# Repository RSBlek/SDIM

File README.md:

# SDIM
Semi Dynamic Indicator Module

Eagle Files for VW Golf 7 Semi Dynamic Indicator Modules for led rear lights

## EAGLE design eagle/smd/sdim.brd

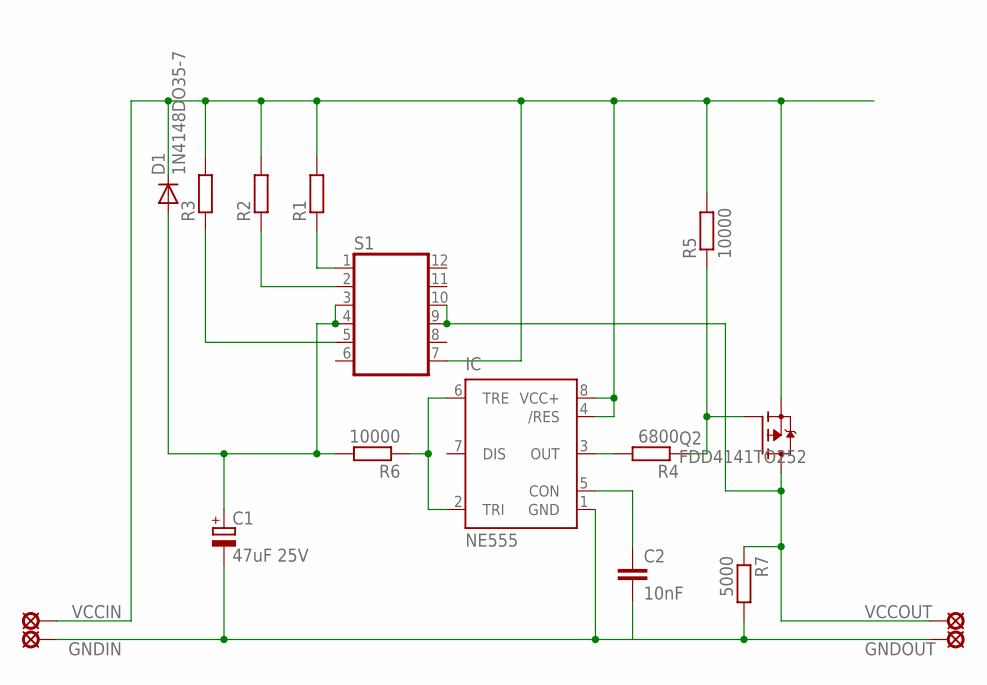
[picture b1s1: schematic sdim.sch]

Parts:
C1: 47uF 25V; E2,5-6
C2: 10nF; C1206
D1: 1N4148DO35-7; DO35-7
GNDIN: MCS10B
GNDOUT: MCS10B
IC: NE555; DIL-08
Q2: FDD4141TO252; TO252
R1, R2, R3: R-EU_R1206; R1206
R4: 6800; R1206
R5, R6: 10000; R1206
R7: 5000; R1206
S1: DA06; DA-06
VCCIN: MCS10B
VCCOUT: MCS10B

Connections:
unnamed: C1.-, C2.2, GNDIN.MP, GNDOUT.MP, IC.1 (GND), R7.2
unnamed: Q2.1 (G), R4.1, R5.1
unnamed: C2.1, IC.5 (CON)
unnamed: R1.1, S1.1
unnamed: R2.1, S1.2
unnamed: IC.3 (OUT), R4.2
unnamed: C1.+, D1.A, R6.2, S1.3, S1.4
unnamed: R3.1, S1.5
unnamed: Q2.3 (D), R7.1, S1.9, S1.10, VCCOUT.MP
unnamed: D1.C, IC.4 (/RES), IC.8 (VCC+), Q2.2 (S), R1.2, R2.2, R3.2, R5.2, S1.7, VCCIN.MP
unnamed: IC.2 (TRI), IC.6 (TRE), R6.1

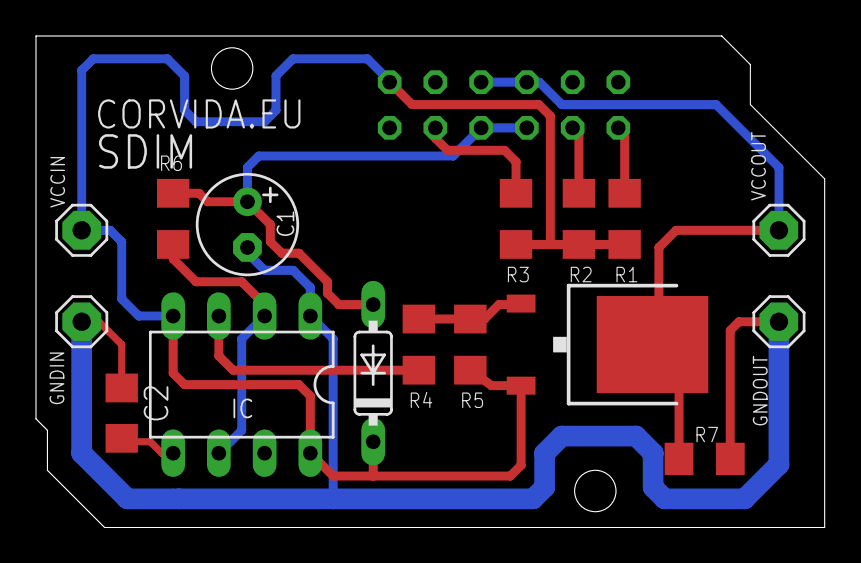
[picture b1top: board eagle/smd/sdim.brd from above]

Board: 2 copper layers, 43.8 x 27.3 mm, 17 parts (1 on the bottom side), 11 nets.

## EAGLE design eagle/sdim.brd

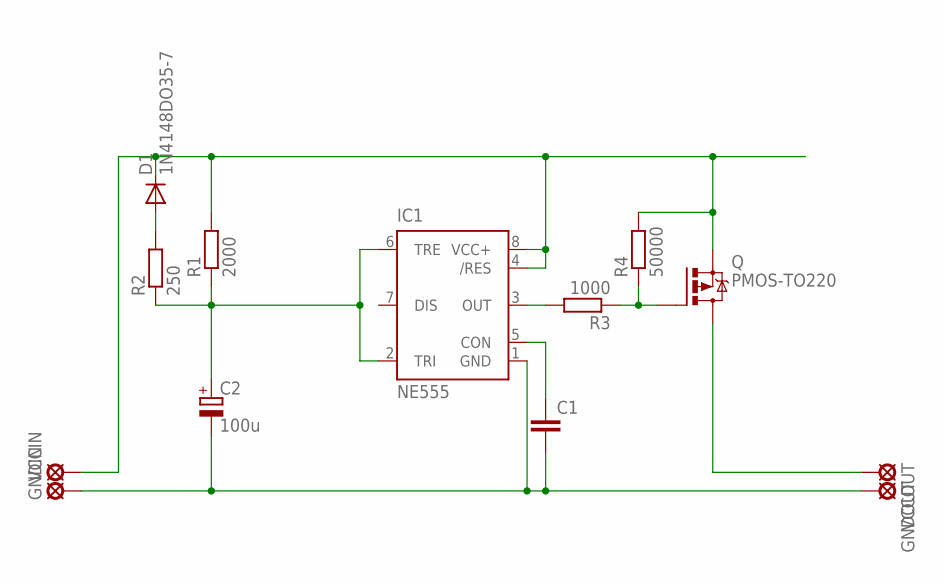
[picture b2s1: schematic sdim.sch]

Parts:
C1: C-EU025-025X050; C025-025X050
C2: 100u; E2,5-6
D1: 1N4148DO35-7; DO35-7
GNDIN: MCS10B
GNDOUT: MCS10B
IC1: NE555; DIL-08
Q: PMOS-TO220; TO220BH
R1: 2000; 0207/7
R2: 250; 0207/7
R3: 1000; 0207/7
R4: 50000; 0207/7
VCCIN: MCS10B
VCCOUT: MCS10B

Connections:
unnamed: C1.2, C2.-, GNDIN.MP, GNDOUT.MP, IC1.1 (GND)
unnamed: D1.A, R2.2
unnamed: D1.C, IC1.4 (/RES), IC1.8 (VCC+), Q.S, R1.2, R4.2, VCCIN.MP
unnamed: C1.1, IC1.5 (CON)
unnamed: IC1.3 (OUT), R3.2
unnamed: Q.G, R3.1, R4.1
unnamed: Q.D, VCCOUT.MP
unnamed: C2.+, IC1.2 (TRI), IC1.6 (TRE), R1.1, R2.1

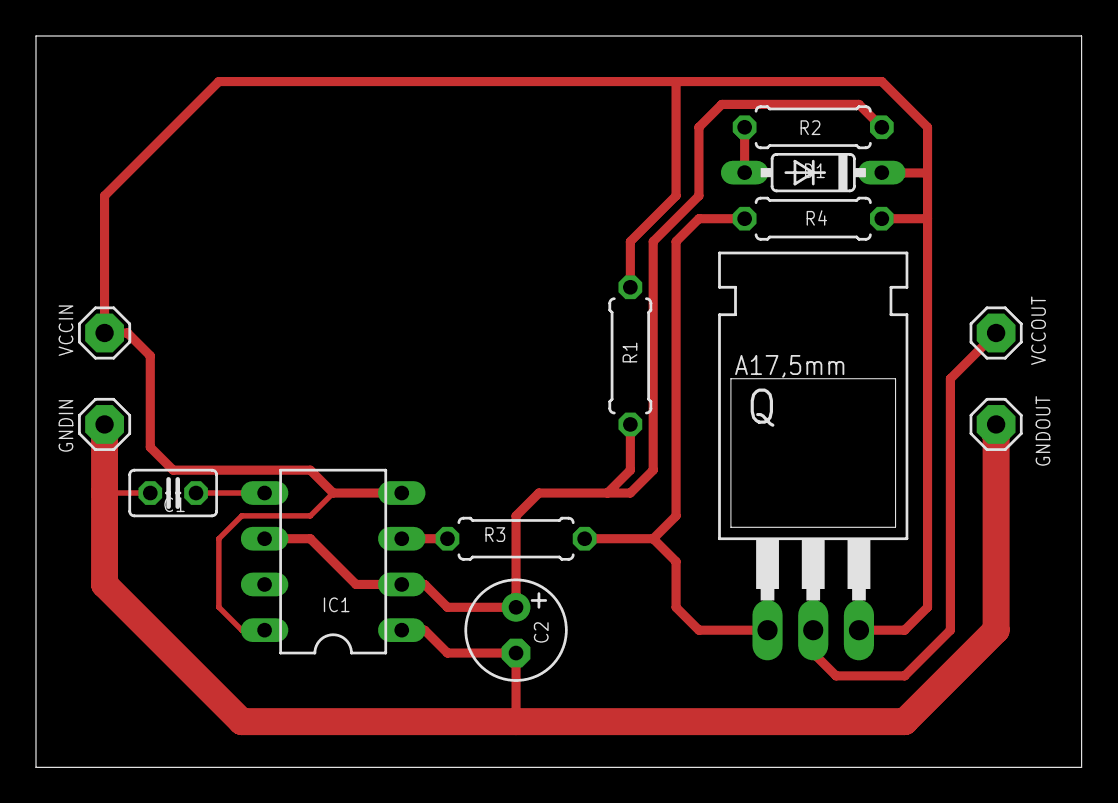
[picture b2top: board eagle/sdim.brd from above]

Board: 2 copper layers, 58.1 x 40.6 mm, 13 parts (0 on the bottom side), 8 nets.

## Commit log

2018-05-31 Added small pcb version
2018-06-06 smaller
2018-06-11 Added very small version
2018-06-12 Made smaller
2018-06-26 Added 2p4t lbr
2018-07-02 Removed useless sht
2018-07-22 Fertig smd
2018-09-09 Added Space between smd and made capacitor 1206
